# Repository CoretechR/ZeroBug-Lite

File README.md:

# ZeroBug Lite

Zerobug Lite is a minimalistic version of the ZeroBug Hexapod robot. By porting the microcontroller's features to Python, the robot can be fully controlled with only the Rasbperry Pi and an updated PCB.

This is a somewhat experimental build. Use at your own risk!

For CAD files, see the original project: https://github.com/CoretechR/ZeroBug

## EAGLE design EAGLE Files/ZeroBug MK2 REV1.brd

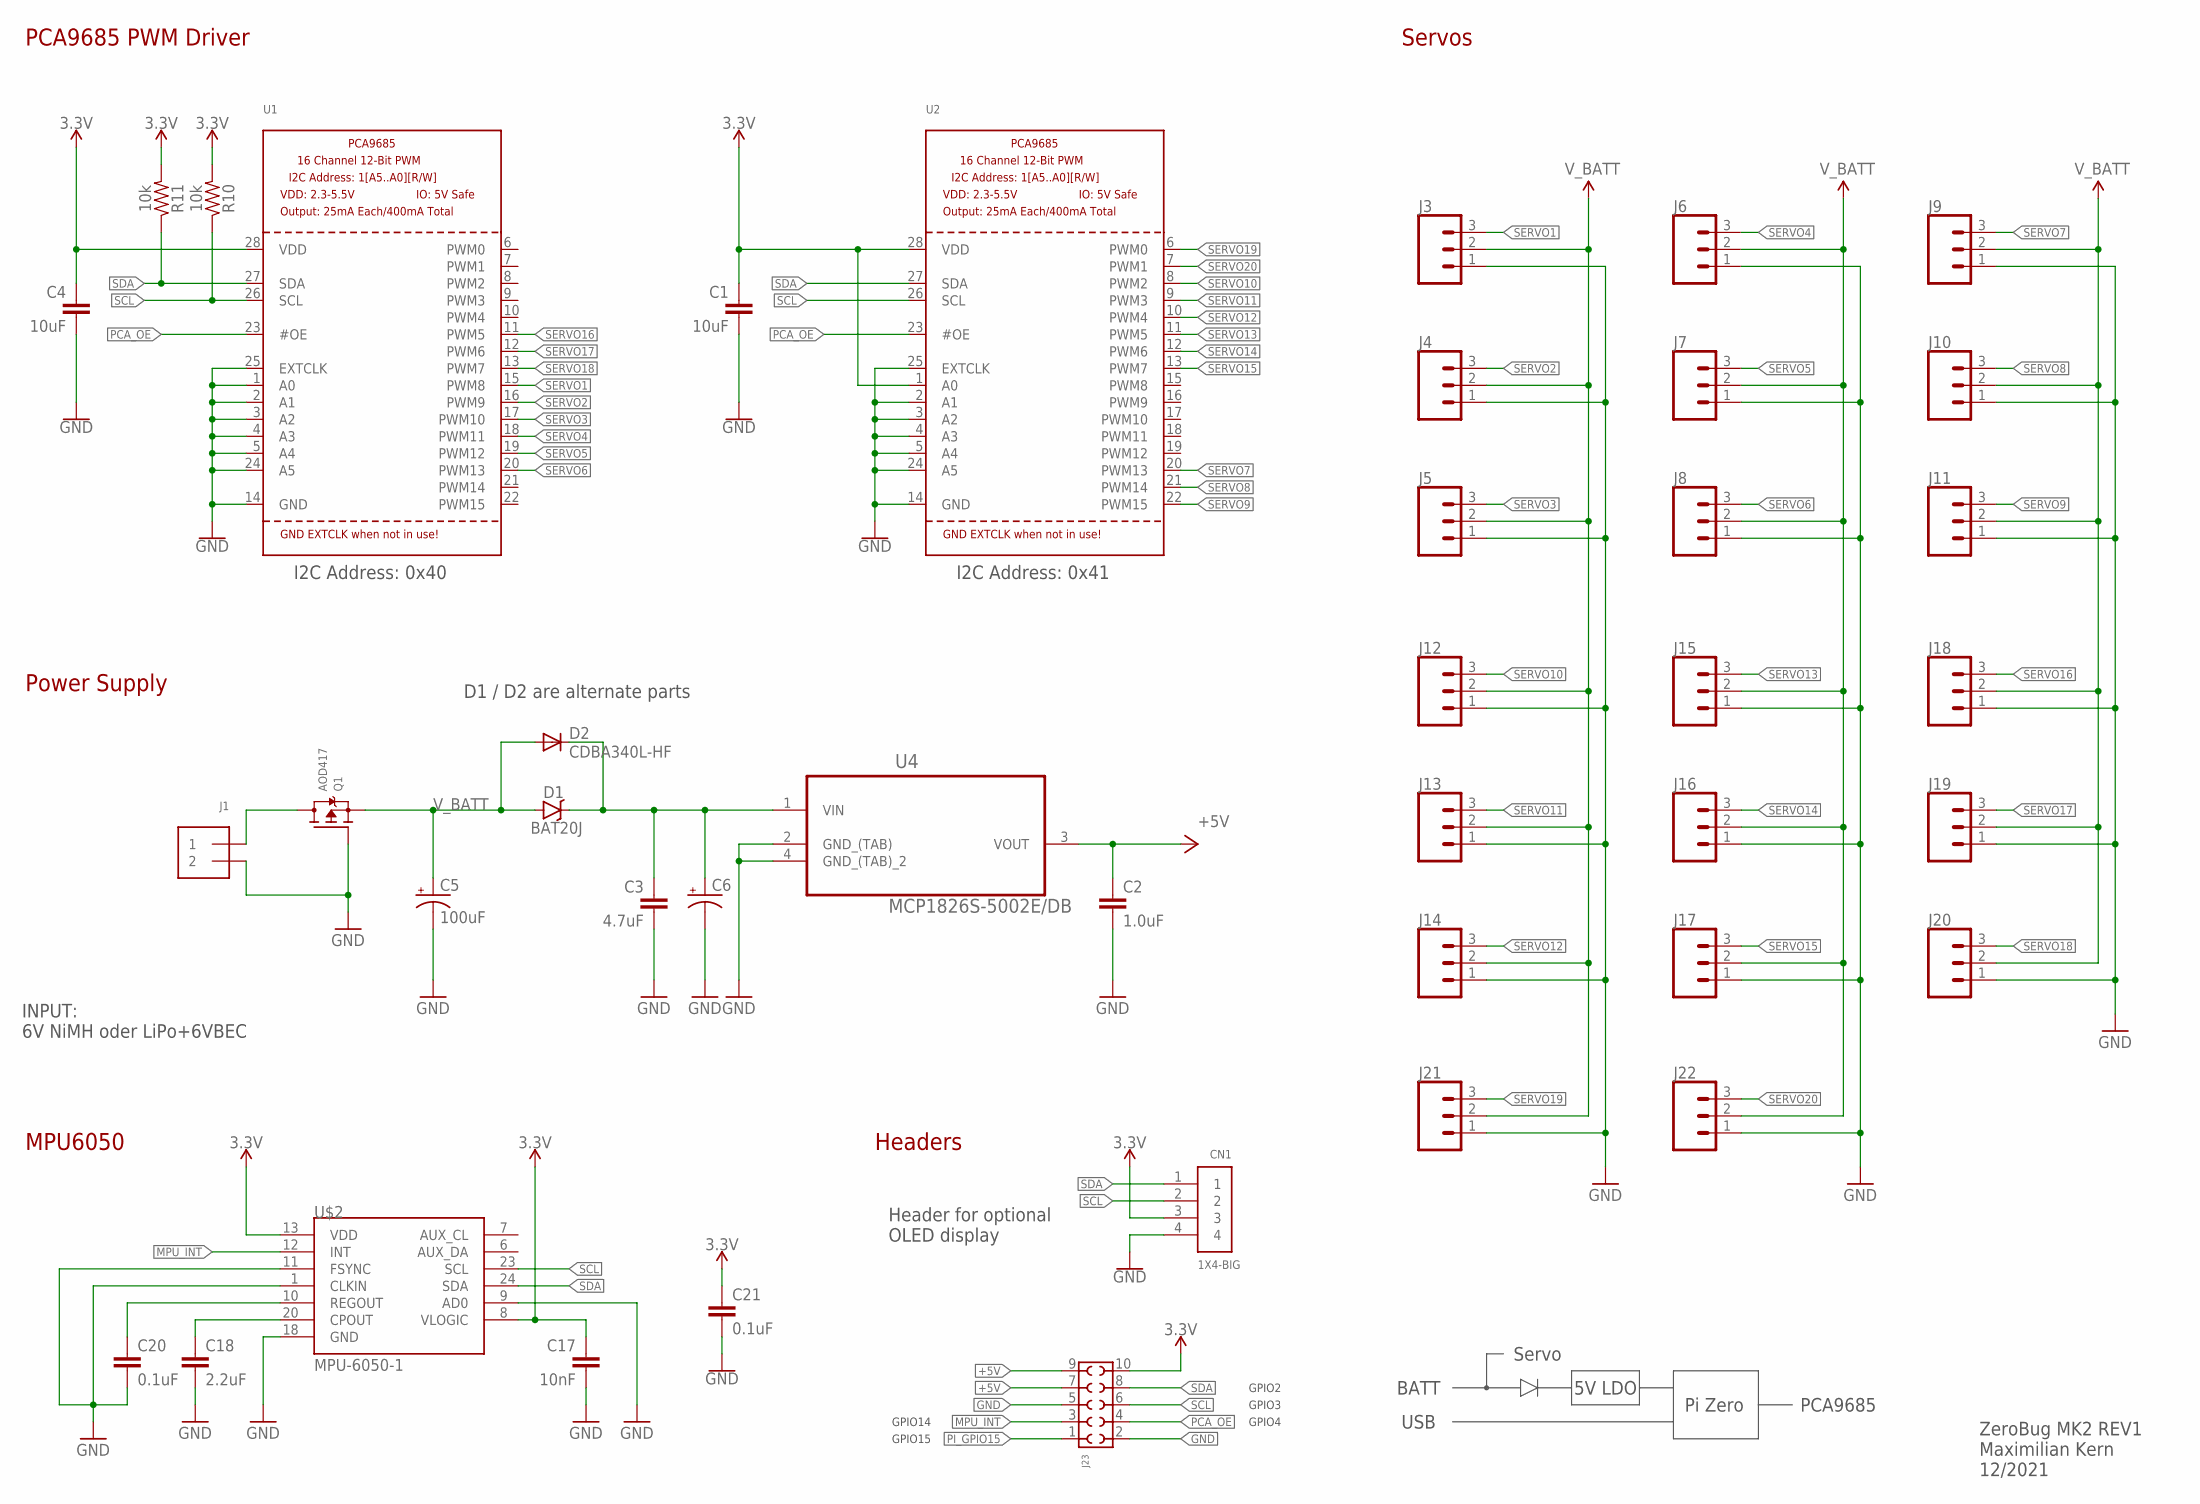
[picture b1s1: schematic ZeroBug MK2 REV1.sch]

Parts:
C1, C4: 10uF; 0805
C2: 1.0uF; 0805
C3: 4.7uF; 0805
C5: 100uF; PANASONIC_D
C6: CPOL-USE5-10.5; E5-10,5
C17: 10nF; 0603
C18: 2.2uF; 0805
C20, C21: 0.1uF; 0603
CN1: 1X4-BIG; 1X04-BIG
D1: BAT20J; SOD-323
D2: CDBA340L-HF; DO-214AC
J1: TERMBLOCK_1X2; TERMBLOCK_1X2-3.5MM
J3, J4, J5, J6, J7, J8, J9, J10, J11, J12, J13, J14, J15, J16, J17, J18, J19, J20, J21, J22: CONN_03; 1X03
J23: 6103XX21821_61031021821; 61031021821
Q1: AOD417; TO252
R10, R11: 10k; 0603
U1, U2: PCA9685; TSSOP28
U4: MCP1826S-5002E/DB; SOT230P700X180-4N
U$2: MPU-6050-1; QFN-24-4MM2

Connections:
3.3V: C1.1, C4.1, C17.1, C21.1, CN1.3, J23.10, R10.2, R11.2, U1.28 (VDD), U2.1 (A0), U2.28 (VDD), U$2.8 (VLOGIC), U$2.13 (VDD)
+5V: C2.1, J23.7, J23.9, U4.3 (VOUT)
GND: C1.2, C2.2, C3.2, C4.2, C5.-, C6.-, C17.2, C18.2, C20.2, C21.2, CN1.4, J1.2, J3.1, J4.1, J5.1, J6.1, J7.1, J8.1, J9.1, J10.1, J11.1, J12.1, J13.1, J14.1, J15.1, J16.1, J17.1, J18.1, J19.1, J20.1, J21.1, J22.1, J23.2, J23.5, Q1.1 (G), U1.1 (A0), U1.2 (A1), U1.3 (A2), U1.4 (A3), U1.5 (A4), U1.14 (GND), U1.24 (A5), U1.25 (EXTCLK), U2.2 (A1), U2.3 (A2), U2.4 (A3), U2.5 (A4), U2.14 (GND), U2.24 (A5), U2.25 (EXTCLK), U4.2 (GND_(TAB)), U4.4 (GND_(TAB)_2), U$2.1 (CLKIN), U$2.9 (AD0), U$2.11 (FSYNC), U$2.18 (GND)
MPU_INT: J23.3, U$2.12 (INT)
unnamed: C3.1, C6.+, D1.C, D2.C, U4.1 (VIN)
unnamed: J1.1, Q1.3 (D)
unnamed: C18.1, U$2.20 (CPOUT)
unnamed: C20.1, U$2.10 (REGOUT)
PCA_OE: J23.4, U1.23 (#OE), U2.23 (#OE)
PI_GPIO15: J23.1
SCL: CN1.2, J23.6, R10.1, U1.26 (SCL), U2.26 (SCL), U$2.23 (SCL)
SDA: CN1.1, J23.8, R11.1, U1.27 (SDA), U2.27 (SDA), U$2.24 (SDA)
SERVO1: J3.3, U1.15 (PWM8)
SERVO2: J4.3, U1.16 (PWM9)
SERVO3: J5.3, U1.17 (PWM10)
SERVO4: J6.3, U1.18 (PWM11)
SERVO5: J7.3, U1.19 (PWM12)
SERVO6: J8.3, U1.20 (PWM13)
SERVO7: J9.3, U2.20 (PWM13)
SERVO8: J10.3, U2.21 (PWM14)
SERVO9: J11.3, U2.22 (PWM15)
SERVO10: J12.3, U2.8 (PWM2)
SERVO11: J13.3, U2.9 (PWM3)
SERVO12: J14.3, U2.10 (PWM4)
SERVO13: J15.3, U2.11 (PWM5)
SERVO14: J16.3, U2.12 (PWM6)
SERVO15: J17.3, U2.13 (PWM7)
SERVO16: J18.3, U1.11 (PWM5)
SERVO17: J19.3, U1.12 (PWM6)
SERVO18: J20.3, U1.13 (PWM7)
SERVO19: J21.3, U2.6 (PWM0)
SERVO20: J22.3, U2.7 (PWM1)
V_BATT: C5.+, D1.A, D2.A, J3.2, J4.2, J5.2, J6.2, J7.2, J8.2, J9.2, J10.2, J11.2, J12.2, J13.2, J14.2, J15.2, J16.2, J17.2, J18.2, J19.2, J20.2, J21.2, J22.2, Q1.2 (S)

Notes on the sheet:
ZeroBug MK2 REV1 Maximilian Kern 12/2021
INPUT: 6V NiMH oder LiPo+6VBEC
5V LDO
Pi Zero
Servo
BATT
USB
PCA9685
MPU6050
Servos
PCA9685 PWM Driver
Headers
Power Supply
GPIO4
GPIO2
GPIO3
GPIO14
GPIO15
I2C Address: 0x40
I2C Address: 0x41
D1 / D2 are alternate parts
Header for optional OLED display

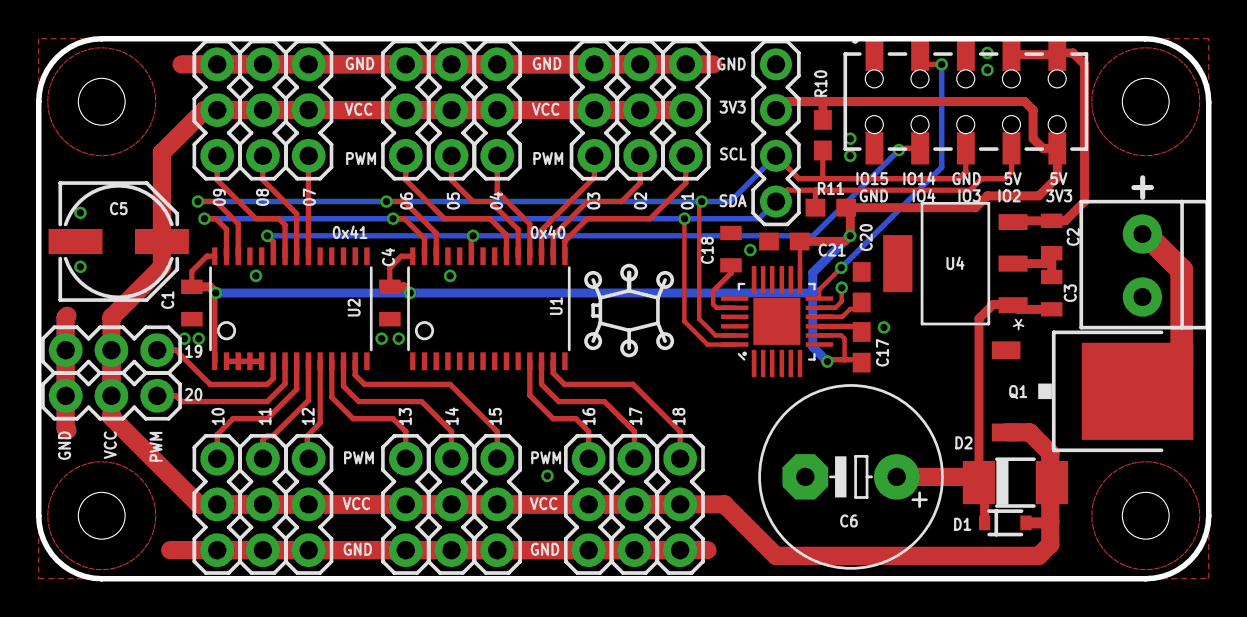
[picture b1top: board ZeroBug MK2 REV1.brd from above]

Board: 2 copper layers, 65.0 x 30.0 mm, 42 parts (0 on the bottom side), 32 nets.

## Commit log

2022-06-17 BOM added
2026-02-15 removed debug line
    - fixed debug line that caused robot to walk in y-direction by itself
    - System shutdown command should work now

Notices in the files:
parts and their libraries:
SparkFun-Capacitors: Licensing: Creative Commons ShareAlike 4.0 International - https://creativecommons.org/licenses/by-sa/4.0
Eagle_WR-PHD: Copyright: Würth Elektronik
